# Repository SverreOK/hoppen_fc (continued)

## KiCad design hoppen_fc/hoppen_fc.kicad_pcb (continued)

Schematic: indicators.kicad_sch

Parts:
B1: FUET-5030; BUZ-SMD_FST-5030; LCSC C391031
C64: 10u; C_0805_2012Metric; LCSC C440198
C65, C66, C67, C68: 100n; C_0402_1005Metric; LCSC C307331
D6: 1N4148W; D_SOD-123; LCSC C2099
D7: GREEN 0805; LED_0805_2012Metric; LCSC C2297
D8: BLUE 0805; LED_0805_2012Metric; LCSC C84256
D9, D10, D11, D12: SK6812; LED-SMD_4P-L2.0-W2.0-BR; LCSC C2909058
Q2: MMBT3904; SOT-23; LCSC C7420353
R34, R36: 1k; R_0402_1005Metric; LCSC C106235
R35: 220R; R_0402_1005Metric; LCSC C25091
R37: 10k; R_0402_1005Metric; LCSC C25744
R38: 22R; R_0402_1005Metric; LCSC C2929994
U17: 74AHCT1G125; SOT-23-5; LCSC C20617903

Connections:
+3V3: B1.1 (POS), C64.1, D6.1 (K); also elsewhere on the board
+5V: C65.1, C66.1, C67.1, C68.1, D9.1 (VDD), D10.1 (VDD), D11.1 (VDD), D12.1 (VDD), U17.5 (VCC); also elsewhere on the board
/Architecture/Indicators/ADD_LED_D_0: D9.4 (DIN), R38.2
/Architecture/Indicators/ADD_LED_D_1: D9.2 (DOUT), D10.4 (DIN)
/Architecture/Indicators/ADD_LED_D_2: D10.2 (DOUT), D11.4 (DIN)
/Architecture/Indicators/ADD_LED_D_3: D11.2 (DOUT), D12.4 (DIN)
/Architecture/Indicators/BUZZER_BASE: Q2.1 (B), R35.2, R37.2
/Architecture/Indicators/BUZZER_N: B1.2 (NEG), D6.2 (A), Q2.3 (C)
/Architecture/Indicators/LED_1: D7.1 (K), R34.1
/Architecture/Indicators/LED_2: D8.1 (K), R36.1
/Architecture/Indicators/PRE_ADD_LED_D_0: R38.1, U17.4
/Architecture/MCU IO/ADD_LED: U17.2; also elsewhere on the board
/Architecture/MCU IO/BUZZER: R35.1; also elsewhere on the board
/Architecture/MCU IO/DBG_LED_1: D7.2 (A); also elsewhere on the board
/Architecture/MCU IO/DBG_LED_2: D8.2 (A); also elsewhere on the board
GND: C64.2, C65.2, C66.2, C67.2, C68.2, D9.3 (GND), D10.3 (GND), D11.3 (GND), D12.3 (GND), Q2.2 (E), R34.2, R36.2, R37.1, U17.1, U17.3 (GND); also elsewhere on the board

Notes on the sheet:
ADDRESSABLE LED
DEBUG LEDs
BUZZER
[${#}] ${TITLE}
DESIGN: Max current is 110 mA

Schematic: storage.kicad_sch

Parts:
C52: 10u; C_0805_2012Metric; LCSC C440198
C53, C54: 100n; C_0402_1005Metric; LCSC C307331
J3: MicroSD Card Holder; microSD_HC_Hirose_DM3D-SF; LCSC C719027
R25, R28, R29: 47k; R_0402_1005Metric; LCSC C25792
R26, R27: 22R; R_0402_1005Metric; LCSC C2929994
R30, R31: 10k; R_0402_1005Metric; LCSC C25744
TP36, TP37, TP38, TP39, TP40, TP41, TP42, TP43, TP44, TP45, TP46, TP47, TP48, TP49: TestPoint; TestPoint_Pad_1.0x1.0mm
U12: W25Q128JVS; SOIC-8_5.3x5.3mm_P1.27mm; LCSC C97521
U13: FM24C64B; SOIC-8_3.9x4.9mm_P1.27mm; LCSC C79988

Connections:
+3V3: C52.1, C53.1, C54.1, J3.4 (VDD), R25.1, R28.2, R29.2, R30.2, R31.2, U12.8 (VCC), U13.8 (VDD); also elsewhere on the board
/Architecture/MCU IO/CARD_DETECT: J3.10 (A), R29.1; also elsewhere on the board
/Architecture/MCU IO/I2C_SCL: R31.1, TP48.1, U13.6 (SCL); also elsewhere on the board
/Architecture/MCU IO/I2C_SDA: R30.1, TP47.1, U13.5 (SDA); also elsewhere on the board
/Architecture/MCU IO/QSPI_CLK: R27.1; also elsewhere on the board
/Architecture/MCU IO/QSPI_IO0: TP36.1, U12.5 (DI/IO_{0}); also elsewhere on the board
/Architecture/MCU IO/QSPI_IO1: TP39.1, U12.2 (DO/IO_{1}); also elsewhere on the board
/Architecture/MCU IO/QSPI_IO2: TP42.1, U12.3 (~WP/IO_{2}); also elsewhere on the board
/Architecture/MCU IO/QSPI_IO3: TP45.1, U12.7 (~HOLD/~RESET/IO_{3}); also elsewhere on the board
/Architecture/MCU IO/QSPI_nCS: R28.1, TP40.1, U12.1 (~CS); also elsewhere on the board
/Architecture/MCU IO/SD_CLK: R26.1; also elsewhere on the board
/Architecture/MCU IO/SD_CMD: J3.3 (CMD), R25.2, TP41.1; also elsewhere on the board
/Architecture/MCU IO/SD_D0: J3.7 (DAT0), TP43.1; also elsewhere on the board
/Architecture/MCU IO/SD_D1: J3.8 (DAT1), TP46.1; also elsewhere on the board
/Architecture/MCU IO/SD_D2: J3.1 (DAT2), TP49.1; also elsewhere on the board
/Architecture/MCU IO/SD_D3: J3.2 (DAT3/CD), TP38.1; also elsewhere on the board
/Architecture/Storage/QSPI_CLK_T: R27.2, TP37.1, U12.6 (CLK)
/Architecture/Storage/SD_CLK_T: J3.5 (CLK), R26.2, TP44.1
GND: C52.2, C53.2, C54.2, J3.6 (VSS), J3.9 (B), J3.11 (SHIELD), U12.4 (GND), U13.1 (A0), U13.2 (A1), U13.3 (A2), U13.4 (VSS), U13.7 (WP); also elsewhere on the board

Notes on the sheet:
FLASH 128 Mb
EEPROM
PROBING
SD CARD
DESIGN: CARD DETECT = LOW when CARD inserted
[${#}] ${TITLE}

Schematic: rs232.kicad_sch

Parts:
C55, C56, C57, C58, C59: 100n; C_0402_1005Metric; LCSC C307331
TP50, TP51: TestPoint; TestPoint_Pad_1.0x1.0mm
U14: SP3223; TSSOP-16_L5.0-W4.4-P0.65-LS6.4-BL; LCSC C2671803

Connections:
+3V3: C55.1, U14.16 (VCC); also elsewhere on the board
/Architecture/Interfaces - Sensors/VN_RS232_RX: U14.13 (R1IN); also elsewhere on the board
/Architecture/Interfaces - Sensors/VN_RS232_TX: U14.14 (T1OUT); also elsewhere on the board
/Architecture/MCU IO/RS232_IN_RX: TP51.1, U14.12 (R1OUT); also elsewhere on the board
/Architecture/MCU IO/RS232_IN_TX: TP50.1, U14.11 (T1IN); also elsewhere on the board
/Architecture/RS232/RS232_C1_N: C56.2, U14.3 (C1-)
/Architecture/RS232/RS232_C1_P: C56.1, U14.1 (C1+)
/Architecture/RS232/RS232_C2_N: C59.2, U14.5 (C2-)
/Architecture/RS232/RS232_C2_P: C59.1, U14.4 (C2+)
/Architecture/RS232/RS232_V_N: C57.1, U14.6 (V-)
/Architecture/RS232/RS232_V_P: C58.1, U14.2 (V+)
GND: C55.2, C57.2, C58.2, U14.15 (GND); also elsewhere on the board

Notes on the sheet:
[${#}] ${TITLE}

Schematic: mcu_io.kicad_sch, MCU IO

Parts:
C23, C24, C25: 100n; C_0402_1005Metric; LCSC C307331
C26, C27, C28, C29: 10p; C_0402_1005Metric; LCSC C32949
JP1, JP2: J; SolderJumper-2_P1.3mm_Bridged_RoundedPad1.0x1.5mm
R1: 10k; R_0402_1005Metric; LCSC C25744
SW1, SW2, SW3: SW_Push; SW-SMD_L3.9-W3.0-P4.45; LCSC C720477
U1: STM32H743ZITx; LQFP-144_20x20mm_P0.5mm; LCSC C114408
U2: PD4E1U; SOT-363_SC-70-6; LCSC C194628
Y1: 25 MHz Crystal; Crystal_SMD_3225-4Pin_3.2x2.5mm; LCSC C9006
Y2: 32.768 kHz; Crystal_SMD_3215-2Pin; LCSC C32346

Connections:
+3V3: JP2.2 (B); also elsewhere on the board
/Architecture/FDCAN/FDCAN1_RX: U1.114 (PD0); also elsewhere on the board
/Architecture/FDCAN/FDCAN1_TX: U1.115 (PD1); also elsewhere on the board
/Architecture/FDCAN/FDCAN2_RX: U1.73 (PB12); also elsewhere on the board
/Architecture/FDCAN/FDCAN2_TX: U1.74 (PB13); also elsewhere on the board
/Architecture/Interfaces - Actuators/ESC_TX_1: U1.58 (PE7); also elsewhere on the board
/Architecture/Interfaces - Actuators/ESC_TX_2: U1.29 (PC3_C); also elsewhere on the board
/Architecture/Interfaces - Actuators/PWM1: U1.60 (PE9); also elsewhere on the board
/Architecture/Interfaces - Actuators/PWM2: U1.35 (PA1); also elsewhere on the board
/Architecture/Interfaces - Actuators/PWM3: U1.81 (PD12); also elsewhere on the board
/Architecture/Interfaces - Actuators/PWM4: U1.82 (PD13); also elsewhere on the board
/Architecture/Interfaces - Actuators/PWM5: U1.85 (PD14); also elsewhere on the board
/Architecture/Interfaces - Actuators/PWM6: U1.86 (PD15); also elsewhere on the board
/Architecture/Interfaces - Comms/EXT_UART_RX: U1.133 (PB3); also elsewhere on the board
/Architecture/Interfaces - Comms/EXT_UART_TX: U1.134 (PB4); also elsewhere on the board
/Architecture/Interfaces - Comms/NRST: C24.1, SW2.1, U1.25 (NRST), U2.3 (D2+); also elsewhere on the board
/Architecture/Interfaces - Comms/SWCLK: U1.109 (PA14); also elsewhere on the board
/Architecture/Interfaces - Comms/SWDIO: U1.105 (PA13); also elsewhere on the board
/Architecture/Interfaces - Sensors/LIDAR1_UART_RX: U1.141 (PE0); also elsewhere on the board
/Architecture/Interfaces - Sensors/LIDAR1_UART_TX: U1.142 (PE1); also elsewhere on the board
/Architecture/Interfaces - Sensors/LIDAR2_UART_RX: U1.139 (PB8); also elsewhere on the board
/Architecture/Interfaces - Sensors/LIDAR2_UART_TX: U1.140 (PB9); also elsewhere on the board
/Architecture/Interfaces - Sensors/RTK_UART_RX: U1.122 (PD6); also elsewhere on the board
/Architecture/Interfaces - Sensors/RTK_UART_TX: U1.119 (PD5); also elsewhere on the board
/Architecture/Interfaces - Sensors/VN_UART_RX: U1.97 (PC7); also elsewhere on the board
/Architecture/Interfaces - Sensors/VN_UART_TX: U1.96 (PC6); also elsewhere on the board
/Architecture/MCU IO/+5V_VMON: U1.53 (PF13); also elsewhere on the board
/Architecture/MCU IO/+BAT_IMON: U1.14 (PF4); also elsewhere on the board
/Architecture/MCU IO/+BAT_VMON: U1.49 (PF11); also elsewhere on the board
/Architecture/MCU IO/ADD_LED: U1.135 (PB5); also elsewhere on the board
/Architecture/MCU IO/BARO_CS: U1.7 (PC13); also elsewhere on the board
/Architecture/MCU IO/BOOT: C25.1, R1.2, SW3.1, U1.138 (BOOT0), U2.6 (D1-)
/Architecture/MCU IO/BOOT_POST_SW: JP2.1 (A), SW3.2
/Architecture/MCU IO/BUZZER: U1.137 (PB7); also elsewhere on the board
/Architecture/MCU IO/CARD_DETECT: U1.110 (PA15); also elsewhere on the board
/Architecture/MCU IO/DBG_LED_1: U1.63 (PE10); also elsewhere on the board
/Architecture/MCU IO/DBG_LED_2: U1.64 (PE11); also elsewhere on the board
/Architecture/MCU IO/EXT_BAT_VMON: U1.13 (PF3); also elsewhere on the board
/Architecture/MCU IO/EXT_LED_D: U1.34 (PA0); also elsewhere on the board
/Architecture/MCU IO/HSE_IN: C26.2, U1.23 (PH0), Y1.1
/Architecture/MCU IO/HSE_OUT: C27.2, U1.24 (PH1), Y1.3
/Architecture/MCU IO/I2C_SCL: U1.11 (PF1); also elsewhere on the board
/Architecture/MCU IO/I2C_SDA: U1.10 (PF0); also elsewhere on the board
/Architecture/MCU IO/IMU_ACC_CS: U1.36 (PA2); also elsewhere on the board
/Architecture/MCU IO/IMU_GYRO_CS: U1.40 (PA4); also elsewhere on the board
/Architecture/MCU IO/INT1_ACC: U1.37 (PA3); also elsewhere on the board
/Architecture/MCU IO/INT3_GYRO: U1.44 (PC4); also elsewhere on the board
/Architecture/MCU IO/LSE_IN: C28.2, U1.8 (PC14), Y2.1
/Architecture/MCU IO/LSE_OUT: C29.2, U1.9 (PC15), Y2.2
/Architecture/MCU IO/MAG_CS: U1.3 (PE4); also elsewhere on the board
/Architecture/MCU IO/MAG_INT: U1.2 (PE3); also elsewhere on the board
/Architecture/MCU IO/QSPI_CLK: U1.22 (PF10); also elsewhere on the board
/Architecture/MCU IO/QSPI_IO0: U1.20 (PF8); also elsewhere on the board
/Architecture/MCU IO/QSPI_IO1: U1.21 (PF9); also elsewhere on the board
/Architecture/MCU IO/QSPI_IO2: U1.19 (PF7); also elsewhere on the board
/Architecture/MCU IO/QSPI_IO3: U1.18 (PF6); also elsewhere on the board
/Architecture/MCU IO/QSPI_nCS: U1.136 (PB6); also elsewhere on the board
/Architecture/MCU IO/RADIO_CS: U1.70 (PB11); also elsewhere on the board
/Architecture/MCU IO/RADIO_DIO0: U1.68 (PE15); also elsewhere on the board
/Architecture/MCU IO/RADIO_DIO1: U1.67 (PE14); also elsewhere on the board
/Architecture/MCU IO/RADIO_DIO2: U1.66 (PE13); also elsewhere on the board
/Architecture/MCU IO/RADIO_RST: U1.65 (PE12); also elsewhere on the board
/Architecture/MCU IO/RS232_IN_RX: U1.102 (PA10); also elsewhere on the board
/Architecture/MCU IO/RS232_IN_TX: U1.101 (PA9); also elsewhere on the board
/Architecture/MCU IO/RST_POST_SW: JP1.1 (A), SW2.2
/Architecture/MCU IO/RTK_EVT: U1.117 (PD3); also elsewhere on the board
/Architecture/MCU IO/RTK_PPS: U1.118 (PD4); also elsewhere on the board
/Architecture/MCU IO/SD_CLK: U1.113 (PC12); also elsewhere on the board
/Architecture/MCU IO/SD_CMD: U1.116 (PD2); also elsewhere on the board
/Architecture/MCU IO/SD_D0: U1.98 (PC8); also elsewhere on the board
/Architecture/MCU IO/SD_D1: U1.99 (PC9); also elsewhere on the board
/Architecture/MCU IO/SD_D2: U1.111 (PC10); also elsewhere on the board
/Architecture/MCU IO/SD_D3: U1.112 (PC11); also elsewhere on the board
/Architecture/MCU IO/SPI1_MISO: U1.42 (PA6); also elsewhere on the board
/Architecture/MCU IO/SPI1_MOSI: U1.43 (PA7); also elsewhere on the board
/Architecture/MCU IO/SPI1_SCK: U1.41 (PA5); also elsewhere on the board
/Architecture/MCU IO/SPI2_MISO: U1.75 (PB14); also elsewhere on the board
/Architecture/MCU IO/SPI2_MOSI: U1.76 (PB15); also elsewhere on the board
/Architecture/MCU IO/SPI2_SCK: U1.69 (PB10); also elsewhere on the board
/Architecture/MCU IO/SPI4_MISO: U1.4 (PE5); also elsewhere on the board
/Architecture/MCU IO/SPI4_MOSI: U1.5 (PE6); also elsewhere on the board
/Architecture/MCU IO/SPI4_SCK: U1.1 (PE2); also elsewhere on the board
/Architecture/MCU IO/USB_N: U1.103 (PA11); also elsewhere on the board
/Architecture/MCU IO/USB_P: U1.104 (PA12); also elsewhere on the board
/Architecture/MCU IO/USER_BTN: C23.1, SW1.1, U1.12 (PF2), U2.1 (D1+)
/Architecture/MCU IO/VN_PPS: U1.100 (PA8); also elsewhere on the board
/Architecture/MCU IO/VN_SYNC: U1.93 (PG8); also elsewhere on the board
GND: C23.2, C24.2, C25.2, C26.1, C27.1, C28.1, C29.1, JP1.2 (B), R1.1, SW1.2, U2.2 (GND), Y1.2, Y1.4; also elsewhere on the board

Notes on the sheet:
SPI4
https://community.st.com/t5/stm32-mcus/how-to-select-a-compatible-crystal-and-load-capacitors-for-stm32/ta-p/780236
USB
QSPI
HSE 25 MHz
POWER MONITORING
SPI1
EXT. UART
SDMMC
BOOT
FDCAN1 & FDCAN2
SERIAL WIRE DEBUG
LIDAR1 & LIDAR2
I2C
PWM
VN300
RESET BUTTON
LSE 32.768 kHz
RTK GNSS
SPI2
ESD PROTECTION
USER BUTTON
MISC.
[${#}] ${TITLE}
C_S = 7p C_L = 12p C = 2(C_L-C_S)

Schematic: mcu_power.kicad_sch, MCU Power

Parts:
C1, C2: 2u2; C_0603_1608Metric; LCSC C23630
C3: 10u; C_0805_2012Metric; LCSC C440198
C4, C5, C6, C7, C8, C9, C10, C11, C12, C13, C14, C15, C16, C17, C19, C22: 100n; C_0402_1005Metric; LCSC C307331
C18, C20, C21: 1u; C_0402_1005Metric; LCSC C52923
L1: 600R@100MHz; L_0603_1608Metric; LCSC C1002
TP1: TestPoint; TestPoint_Pad_1.0x1.0mm
U1: STM32H743ZITx; LQFP-144_20x20mm_P0.5mm; LCSC C114408

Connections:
+3V3: C3.1, C4.1, C5.1, C6.1, C7.1, C8.1, C9.1, C10.1, C11.1, C12.1, C13.1, C14.1, C15.1, C16.1, C17.1, C20.1, L1.1, U1.6 (VBAT), U1.17 (VDD), U1.30 (VDD), U1.39 (VDD), U1.52 (VDD), U1.62 (VDD), U1.72 (VDD), U1.84 (VDD), U1.95 (VDD33_USB), U1.108 (VDD), U1.121 (VDD), U1.131 (VDD), U1.143 (PDR_ON), U1.144 (VDD); also elsewhere on the board
/Architecture/MCU Power/MCU_VCAP1: C1.1, U1.71 (VCAP)
/Architecture/MCU Power/MCU_VCAP2: C2.1, U1.106 (VCAP)
/Architecture/MCU Power/MCU_VDDA: C18.1, C19.1, C21.1, C22.1, L1.2, TP1.1, U1.32 (VREF+), U1.33 (VDDA)
GND: C1.2, C2.2, C3.2, C4.2, C5.2, C6.2, C7.2, C8.2, C9.2, C10.2, C11.2, C12.2, C13.2, C14.2, C15.2, C16.2, C17.2, C18.2, C19.2, C20.2, C21.2, C22.2, U1.16 (VSS), U1.31 (VSSA), U1.38 (VSS), U1.51 (VSS), U1.61 (VSS), U1.83 (VSS), U1.94 (VSS), U1.107 (VSS), U1.120 (VSS), U1.130 (VSS); also elsewhere on the board

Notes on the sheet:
[${#}] ${TITLE}

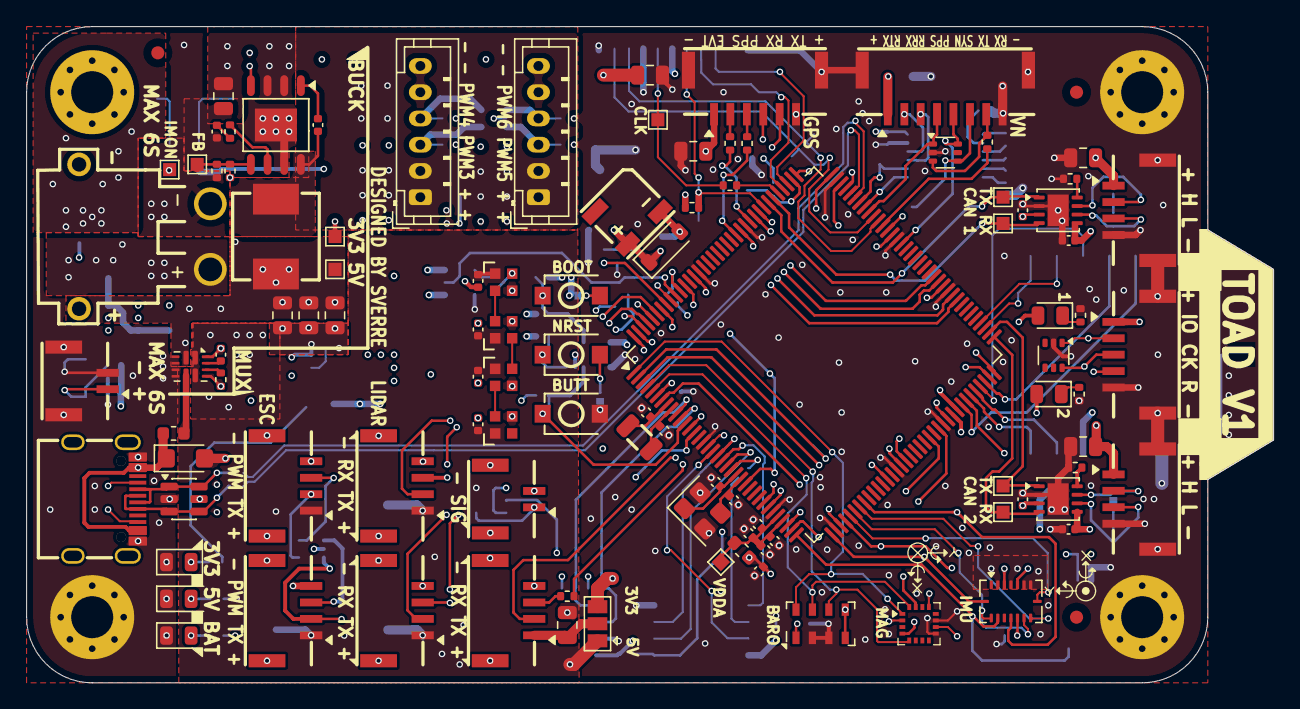
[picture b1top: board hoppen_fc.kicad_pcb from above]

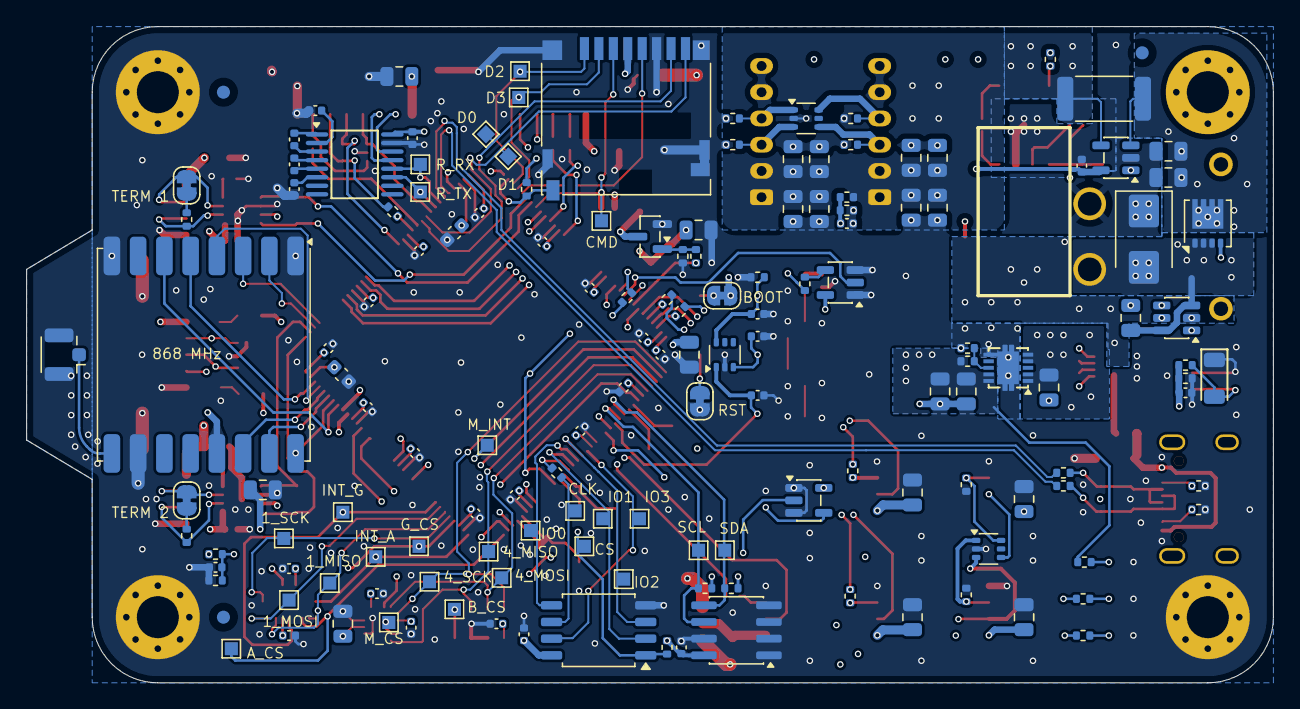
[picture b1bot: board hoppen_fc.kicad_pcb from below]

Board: 6 copper layers, 95.0 x 50.0 mm, 261 parts (151 on the bottom side), 158 nets.

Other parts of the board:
TP5: TestPoint; TestPoint_Pad_1.0x1.0mm

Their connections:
+5V_EXT: TP5.1; also elsewhere on the board

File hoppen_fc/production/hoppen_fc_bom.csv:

Designator,Footprint,Quantity,Value,LCSC Part #
B1,BUZ-SMD_FST-5030,1,FUET-5030,C391031
"C1, C2",0603,2,2u2,C23630
"C10, C11, C12, C13, C14, C15, C16, C17, C19, C22, C23, C24, C25, C33, C35, C39, C4, C44, C45, C46, C47, C48, C5, C50, C53, C54, C55, C56, C57, C58, C59, C6, C60, C61, C62, C63, C65, C66, C67, C68, C7, C8, C85, C9",0402,44,100n,C307331
"C18, C20, C21, C49",0402,4,1u,C52923
"C26, C27, C28, C29",0402,4,10p,C32949
"C3, C30, C31, C32, C34, C51, C52, C64, C73, C74, C75, C76, C77, C78, C79, C80, C81, C82",0805,18,10u,C440198
"C36, C37, C38, C41, C42, C43, C69, C70, C71, C72, C83, C84, C86, C87",0805,14,22u,C45783
C40,0402,1,2n7,C106251
D1,D_SMB,1,SMBJ28CA,C19077583
"D10, D11, D12, D9",LED-SMD_4P-L2.0-W2.0-BR,4,SK6812,C2909058
D13,D_SOD-123FL,1,SMF28CA,C19077517
"D2, D3, D4, D7",0805,4,GREEN 0805,C2297
D5,D_SMF,1,SMF5V0A,C1972946
D6,D_SOD-123,1,1N4148W,C2099
D8,0805,1,BLUE 0805,C84256
F1,0603,1,500 mA @ 6V,C210357
"J10, J11",JST_PH_B6B-PH-K_1x06_P2.00mm_Vertical,2,B6B-PH,
"J12, J13, J17, J4, J5, J8, J9",BM04B-GHS1.25,7,BM04B-GHS1.25,C161692
"J14, J16",BM02B-GHS1.25,2,BM02B-GHS1.25,C225118
J15,BM05B-GHS1.25,1,BM05B-GHS1.25,C225121
J18,U.FL_Hirose_U.FL-R-SMT-1_Vertical,1,U.FL,C88374
J2,USB-C_SMD-TYPE-C-31-M-12_1,1,USB_C_Receptacle_USB2.0_16P,C165948
J3,microSD_HC_Hirose_DM3D-SF,1,MicroSD Card Holder,C719027
J6,BM06B-GHS-1.25,1,BM06B-GHS1.25,C225122 
J7,BM08B-GHS1.25,1,BM08B-GHS1.25,C133062
L1,0603,1,600R@100MHz,C1002
L2,IND-SMD_L7.2-W6.6_GPSR07X0,1,4.7 uH 6A,C5189754
Q1,Diodes_PowerDI3333-8,1,NMOS,C2802568
Q2,SOT-23,1,MMBT3904,C7420353
"R1, R19, R20, R30, R31, R32, R33, R37, R56, R8",0402,10,10k,C25744
"R12, R23, R24",0402,3,5k1,C25905
"R13, R15, R34, R36",0402,4,1k,C106235
R14,0402,1,3k57,C270609
R16,0402,1,1k15,C5159680
"R17, R55",0402,2,100k,C25741
R18,0402,1,33k,C25779
R2,2512,1,5m,C185817
"R21, R22, R26, R27, R38, R39, R40, R41, R42, R43, R44, R45, R46, R57, R58",0402,15,22R,C2929994
"R25, R28, R29, R47, R48, R49, R50, R51, R52",0402,9,47k,C25792
R35,0402,1,220R,C25091
R4,0402,1,53k6,C53398
"R53, R54",0402,2,120R,C25079
R6,0402,1,200k,C25764
R7,0402,1,15k8,C26956
R9,0402,1,20k,C25765
"SW1, SW2, SW3",SW-SMD_L3.9-W3.0-P4.45,3,SW_Push,C720477
"TP1, TP20, TP21, TP22, TP23, TP24, TP25, TP26, TP27, TP28, TP29, TP30, TP31, TP32, TP33, TP34, TP35, TP36, TP37, TP38, TP39, TP40, TP41, TP42, TP43, TP44, TP45, TP46, TP47, TP48, TP49, TP5, TP50, TP51, TP52, TP53, TP54, TP55",TestPoint_Pad_1.0x1.0mm,38,TestPoint,
U1,LQFP-144_20x20mm_P0.5mm,1,STM32H743ZITx,C730184
U10,LGA-16_3x3mm_P0.5mm,1,MMC5983MA,C404329
U11,SOT-23-6,1,USBLC6-2SC6,C7519
U12,SOIC-8_5.3x5.3mm_P1.27mm,1,W25Q128JVS,C97521
U13,SOIC-8_3.9x4.9mm_P1.27mm,1,FM24C64B,C79988
U14,TSSOP-16_L5.0-W4.4-P0.65-LS6.4-BL,1,SP3223,C2671803
"U15, U16",HVSON-8-1EP_3x3mm_P0.65mm_EP1.6x2.4mm,2,TJA1051TK-3,C2875699
"U17, U21",SOT-23-5,2,74AHCT1G125,C20617903
"U18, U19, U2, U20, U22",SOT-363_SC-70-6,5,PD4E1U,C194628
U3,SOT-23-5,1,INA293A,C1855790
U4,SOT-23-6,1,LM74700,C2941042
U5,SO-8-EP,1,AP64500,C2070920
U6,Texas_VQFN-HR-12_2x2.5mm_P0.5mm,1,TPS2121,C2156025
U7,VSON-10,1,TPS74801DRC,C105263
U8,LGA-8_3x5mm_P1.25mm,1,MS5607-02BA,C97627
U9,Bosch_LGA-16_4.5x3mm_P0.5mm_LayoutBorder7x1y_ClockwisePinNumbering,1,BMI088,C194919
Y1,Crystal_SMD_3225-4Pin_3.2x2.5mm,1,25 MHz Crystal,C9006
Y2,Crystal_SMD_3215-2Pin,1,32.768 kHz,C32346

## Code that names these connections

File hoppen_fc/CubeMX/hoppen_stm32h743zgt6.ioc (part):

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Mcu.Name=STM32H743ZGTx
Mcu.Package=LQFP144
Mcu.UserName=STM32H743ZGTx
PA0.GPIOParameters=GPIO_Label
PA0.GPIO_Label=EXT_LED_TIM5_CH1
PA0.Signal=S_TIM5_CH1
PA1.GPIOParameters=GPIO_Label
PA1.GPIO_Label=PWM2_TIM2_CH2
PA1.Signal=S_TIM2_CH2
PA10.GPIOParameters=GPIO_Label
PA10.GPIO_Label=RS232_IN_USART1_RX
PA10.Mode=Asynchronous
PA10.Signal=USART1_RX
PA11.Mode=Device_Only
PA11.Signal=USB_OTG_FS_DM
PA12.Mode=Device_Only
PA12.Signal=USB_OTG_FS_DP
PA13\ (JTMS/SWDIO).Mode=Serial_Wire
PA13\ (JTMS/SWDIO).Signal=DEBUG_JTMS-SWDIO
PA14\ (JTCK/SWCLK).Mode=Serial_Wire
PA14\ (JTCK/SWCLK).Signal=DEBUG_JTCK-SWCLK
PA15\ (JTDI).GPIOParameters=GPIO_Label
PA15\ (JTDI).GPIO_Label=CARD_DETECT
PA15\ (JTDI).Signal=GPIO_Input
PA2.GPIOParameters=GPIO_Label
PA2.GPIO_Label=IMU_ACC_CS
PA2.Signal=GPIO_Output
PA3.GPIOParameters=GPIO_Label
PA3.GPIO_Label=INT1_ACC
PA3.Signal=GPIO_Input
PA4.GPIOParameters=GPIO_Label
PA4.GPIO_Label=IMU_GYRO_CS
PA4.Signal=GPIO_Output
PA5.Mode=Full_Duplex_Master
PA5.Signal=SPI1_SCK
PA6.Mode=Full_Duplex_Master
PA6.Signal=SPI1_MISO
PA7.Mode=Full_Duplex_Master
PA7.Signal=SPI1_MOSI
PA8.GPIOParameters=GPIO_Label
PA8.GPIO_Label=VN_PPS
PA8.Signal=GPIO_Input
PA9.GPIOParameters=GPIO_Label
PA9.GPIO_Label=RS232_IN_USART1_TX
PA9.Mode=Asynchronous
PA9.Signal=USART1_TX
PB10.Mode=Full_Duplex_Master
PB10.Signal=SPI2_SCK
PB11.GPIOParameters=GPIO_Label
PB11.GPIO_Label=RADIO_CS
PB11.Signal=GPIO_Output
PB12.Mode=FDCAN_Activate
PB12.Signal=FDCAN2_RX
PB13.Mode=FDCAN_Activate
PB13.Signal=FDCAN2_TX
PB14.Mode=Full_Duplex_Master
PB14.Signal=SPI2_MISO
PB15.Mode=Full_Duplex_Master
PB15.Signal=SPI2_MOSI
PB3\ (JTDO/TRACESWO).GPIOParameters=GPIO_Label
PB3\ (JTDO/TRACESWO).GPIO_Label=EXT_UART7_RX
PB3\ (JTDO/TRACESWO).Mode=Asynchronous
PB3\ (JTDO/TRACESWO).Signal=UART7_RX
PB4\ (NJTRST).GPIOParameters=GPIO_Label
PB4\ (NJTRST).GPIO_Label=EXT_UART7_TX
PB4\ (NJTRST).Mode=Asynchronous
PB4\ (NJTRST).Signal=UART7_TX
PB5.GPIOParameters=GPIO_Label
PB5.GPIO_Label=LED_TIM3_CH2
PB5.Signal=S_TIM3_CH2
PB6.Mode=Single Bank 1
PB6.Signal=QUADSPI_BK1_NCS
PB7.GPIOParameters=GPIO_Label
PB7.GPIO_Label=BUZZER_TIM17_CH1N
PB7.Mode=PWM Generation1 CH1N
PB7.Signal=TIM17_CH1N
PB8.GPIOParameters=GPIO_Label
PB8.GPIO_Label=LIDAR2_UART4_RX
PB8.Mode=Asynchronous
PB8.Signal=UART4_RX
PB9.GPIOParameters=GPIO_Label
PB9.GPIO_Label=LIDAR2_UART4_TX
PB9.Mode=Asynchronous
PB9.Signal=UART4_TX
PC10.Mode=SD_4_bits_Wide_bus
PC10.Signal=SDMMC1_D2
PC11.Mode=SD_4_bits_Wide_bus
PC11.Signal=SDMMC1_D3
PC12.Mode=SD_4_bits_Wide_bus
PC12.Signal=SDMMC1_CK
PC13.GPIOParameters=GPIO_Label
PC13.GPIO_Label=BARO_CS
PC13.Signal=GPIO_Output
PC14-OSC32_IN\ (OSC32_IN).Mode=LSE-External-Oscillator
PC14-OSC32_IN\ (OSC32_IN).Signal=RCC_OSC32_IN
PC15-OSC32_OUT\ (OSC32_OUT).Mode=LSE-External-Oscillator
PC15-OSC32_OUT\ (OSC32_OUT).Signal=RCC_OSC32_OUT
PC3_C.GPIOParameters=GPIO_Label
PC3_C.GPIO_Label=ESC_TX_2
PC3_C.Signal=GPIO_Output
PC4.GPIOParameters=GPIO_Label
PC4.GPIO_Label=INT3_GYRO
PC4.Signal=GPIO_Input
PC6.GPIOParameters=GPIO_Label
PC6.GPIO_Label=VN_USART6_TX
PC6.Mode=Asynchronous
PC6.Signal=USART6_TX
PC7.GPIOParameters=GPIO_Label
PC7.GPIO_Label=VN_USART6_RX
PC7.Mode=Asynchronous
PC7.Signal=USART6_RX
PC8.Mode=SD_4_bits_Wide_bus
PC8.Signal=SDMMC1_D0
PC9.Mode=SD_4_bits_Wide_bus
PC9.Signal=SDMMC1_D1
PD0.Mode=FDCAN_Activate
PD0.Signal=FDCAN1_RX
PD1.Mode=FDCAN_Activate
PD1.Signal=FDCAN1_TX
PD12.GPIOParameters=GPIO_Label
PD12.GPIO_Label=PWM3
PD12.Signal=S_TIM4_CH1
PD13.GPIOParameters=GPIO_Label
PD13.GPIO_Label=PWM4
PD13.Signal=S_TIM4_CH2
PD14.GPIOParameters=GPIO_Label
PD14.GPIO_Label=PWM5
PD14.Signal=S_TIM4_CH3
PD15.GPIOParameters=GPIO_Label
PD15.GPIO_Label=PWM6
PD15.Signal=S_TIM4_CH4
PD2.Mode=SD_4_bits_Wide_bus
PD2.Signal=SDMMC1_CMD
PD3.GPIOParameters=GPIO_Label
PD3.GPIO_Label=RTK_EVT
PD3.Signal=GPIO_Input
PD4.GPIOParameters=GPIO_Label
PD4.GPIO_Label=RTK_PPS
PD4.Signal=GPIO_Input
PD5.GPIOParameters=GPIO_Label
PD5.GPIO_Label=RTK_USART2_TX
PD5.Mode=Asynchronous
PD5.Signal=USART2_TX
PD6.GPIOParameters=GPIO_Label
PD6.GPIO_Label=RTK_USART2_RX
PD6.Mode=Asynchronous
PD6.Signal=USART2_RX
PE0.GPIOParameters=GPIO_Label
PE0.GPIO_Label=LIDAR1_UART_RX
PE0.Mode=Asynchronous
PE0.Signal=UART8_RX
PE1.GPIOParameters=GPIO_Label
PE1.GPIO_Label=LIDAR1_UART8_TX
PE1.Mode=Asynchronous
PE1.Signal=UART8_TX
PE10.GPIOParameters=GPIO_Label
PE10.GPIO_Label=LED_1
PE10.Signal=GPIO_Output
PE11.GPIOParameters=GPIO_Label
PE11.GPIO_Label=LED_2
PE11.Signal=GPIO_Output
PE12.GPIOParameters=GPIO_Label
PE12.GPIO_Label=RADIO_RST
PE12.Signal=GPIO_Output
PE13.GPIOParameters=GPIO_Label
PE13.GPIO_Label=RADIO_DIO2
PE13.Signal=GPIO_Output
PE14.GPIOParameters=GPIO_Label
PE14.GPIO_Label=RADIO_DIO1
PE14.Signal=GPIO_Output
PE15.GPIOParameters=GPIO_Label
PE15.GPIO_Label=RADIO_DIO0
PE15.Signal=GPIO_Output
PE2.Mode=Full_Duplex_Master
PE2.Signal=SPI4_SCK
PE3.GPIOParameters=GPIO_Label
PE3.GPIO_Label=MAG_INT
PE3.Signal=GPIO_Input
PE4.GPIOParameters=GPIO_Label
PE4.GPIO_Label=MAG_CS
PE4.Signal=GPIO_Output
PE5.Mode=Full_Duplex_Master
PE5.Signal=SPI4_MISO
PE6.Mode=Full_Duplex_Master
PE6.Signal=SPI4_MOSI
PE7.GPIOParameters=GPIO_Label
PE7.GPIO_Label=ESC_RX_1
PE7.Signal=GPIO_Input
PE9.GPIOParameters=GPIO_Label
PE9.GPIO_Label=PWM1_TIM1_CH1
PE9.Signal=S_TIM1_CH1
PF0.Mode=I2C
PF0.Signal=I2C2_SDA
PF1.Mode=I2C
PF1.Signal=I2C2_SCL
PF10.Mode=Single Bank 1
PF10.Signal=QUADSPI_CLK
PF11.GPIOParameters=GPIO_Label
PF11.GPIO_Label=BAT_VMON_ADC1_INP2
PF11.Mode=IN2-Single-Ended
PF11.Signal=ADC1_INP2
PF13.GPIOParameters=GPIO_Label
PF13.GPIO_Label=VMON_ADC2_INP2
PF13.Mode=IN2-Single-Ended
PF13.Signal=ADC2_INP2
PF2.GPIOParameters=GPIO_Label
PF2.GPIO_Label=USER_BTN
PF2.Signal=GPIO_Input
PF3.GPIOParameters=GPIO_Label
PF3.GPIO_Label=EXT_BAT_ADC3_INP5
PF3.Mode=IN5-Single-Ended
PF3.Signal=ADC3_INP5
PF4.GPIOParameters=GPIO_Label
PF4.GPIO_Label=IMON_ADC3_INP9
PF4.Mode=IN9-Single-Ended
PF4.Signal=ADC3_INP9
PF6.Mode=Single Bank 1
PF6.Signal=QUADSPI_BK1_IO3
PF7.Mode=Single Bank 1
PF7.Signal=QUADSPI_BK1_IO2
PF8.Mode=Single Bank 1
PF8.Signal=QUADSPI_BK1_IO0
PF9.Mode=Single Bank 1
PF9.Signal=QUADSPI_BK1_IO1
PG10.GPIOParameters=GPIO_Label
PG10.GPIO_Label=SPI6_CS_2
PG10.Signal=GPIO_Output
PG11.GPIOParameters=GPIO_Label
PG11.GPIO_Label=SPI6_CS_1
PG11.Signal=GPIO_Output
PG12.Mode=Full_Duplex_Master
PG12.Signal=SPI6_MISO
PG13.Mode=Full_Duplex_Master
PG13.Signal=SPI6_SCK
PG14.Mode=Full_Duplex_Master
PG14.Signal=SPI6_MOSI
PG8.GPIOParameters=GPIO_Label
PG8.GPIO_Label=VN_SYNC
PG8.Signal=GPIO_Output
PH0-OSC_IN\ (PH0).Mode=HSE-External-Oscillator
PH0-OSC_IN\ (PH0).Signal=RCC_OSC_IN
PH1-OSC_OUT\ (PH1).Mode=HSE-External-Oscillator
PH1-OSC_OUT\ (PH1).Signal=RCC_OSC_OUT
RCC.SYSCLKFreq_VALUE=64000000
board=custom

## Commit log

2025-12-13 added mcu and some more project changes
2025-12-13 Titleblock and deleted hoppen prl
2025-12-14 more passives work
2025-12-15 sensors done, mcu worked on
2025-12-15 rs232,can,ind,storage,usb v01
2025-12-16 yeah
2025-12-18 wen branch and pr
2025-12-18 much work and .ioc file added
2025-12-22 start fix fp
2025-12-23 reformat structure
2025-12-23 remove radio.sch
2025-12-28 work
2025-12-29 power input/generation reworked
2025-12-29 finished routing, starting doublechecking and componenting
2025-12-31 finished adding lcsc numbers
2026-01-02 ready for routing?
2026-01-05 routing and adding rf module
2026-01-06 misplaced rf lib
2026-01-22 sync
2026-01-27 comments
2026-02-10 bump
2026-02-10 add connectors
2026-03-31 production v1
